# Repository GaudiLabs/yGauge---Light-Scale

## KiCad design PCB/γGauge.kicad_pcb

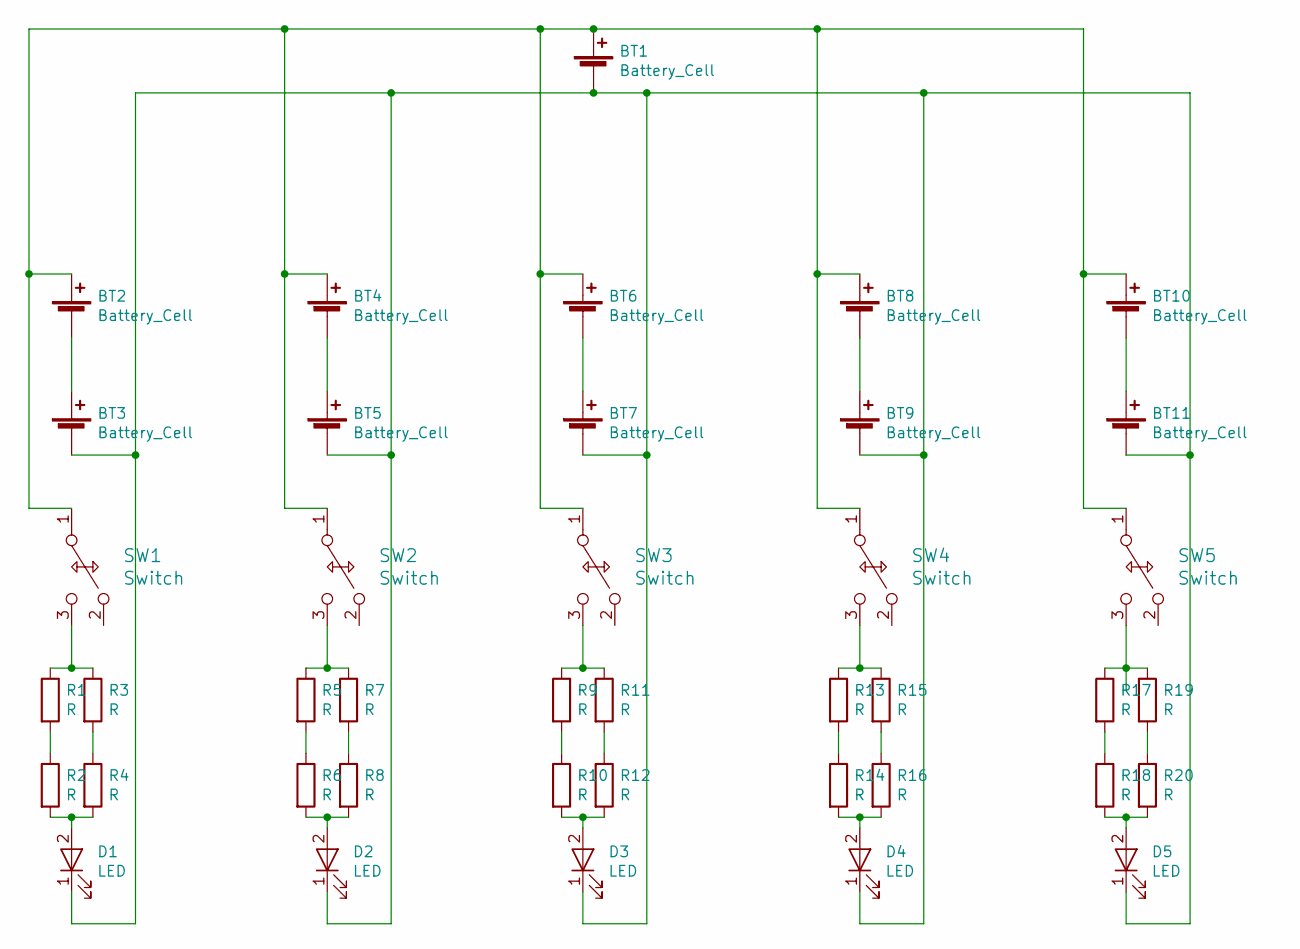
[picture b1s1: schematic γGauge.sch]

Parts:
BT1: Battery_Cell; CR2032_Holder
BT2, BT3, BT4, BT5, BT6, BT7, BT8, BT9, BT10, BT11: Battery_Cell; CELL_HOLDER_6_8
D1, D2, D3, D4, D5: LED; LP_T67K
R1, R2, R3, R4, R5, R6, R7, R8, R9, R10, R11, R12, R13, R14, R15, R16, R17, R18, R19, R20: R; SMD_LowZ
SW1, SW2, SW3, SW4, SW5: Switch; MSS22d18

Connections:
unnamed: BT1.1 (+), BT2.1 (+), BT4.1 (+), BT6.1 (+), BT8.1 (+), BT10.1 (+), SW1.1, SW2.1, SW3.1, SW4.1, SW5.1
unnamed: BT1.2 (-), BT3.2 (-), BT5.2 (-), BT7.2 (-), BT9.2 (-), BT11.2 (-), D1.1 (K), D2.1 (K), D3.1 (K), D4.1 (K), D5.1 (K)
unnamed: BT2.2 (-), BT3.1 (+)
unnamed: BT4.2 (-), BT5.1 (+)
unnamed: BT6.2 (-), BT7.1 (+)
unnamed: BT8.2 (-), BT9.1 (+)
unnamed: BT10.2 (-), BT11.1 (+)
unnamed: D1.2 (A), R2.2, R4.2
unnamed: D2.2 (A), R6.2, R8.2
unnamed: D3.2 (A), R10.2, R12.2
unnamed: D4.2 (A), R14.2, R16.2
unnamed: D5.2 (A), R18.2, R20.2
unnamed: R1.1, R3.1, SW1.3
unnamed: R1.2, R2.1
unnamed: R3.2, R4.1
unnamed: R5.1, R7.1, SW2.3
unnamed: R5.2, R6.1
unnamed: R7.2, R8.1
unnamed: R9.2, R10.1
unnamed: R9.1, R11.1, SW3.3
unnamed: R11.2, R12.1
unnamed: R13.1, R15.1, SW4.3
unnamed: R13.2, R14.1
unnamed: R15.2, R16.1
unnamed: R17.1, R19.1, SW5.3
unnamed: R17.2, R18.1
unnamed: R19.2, R20.1

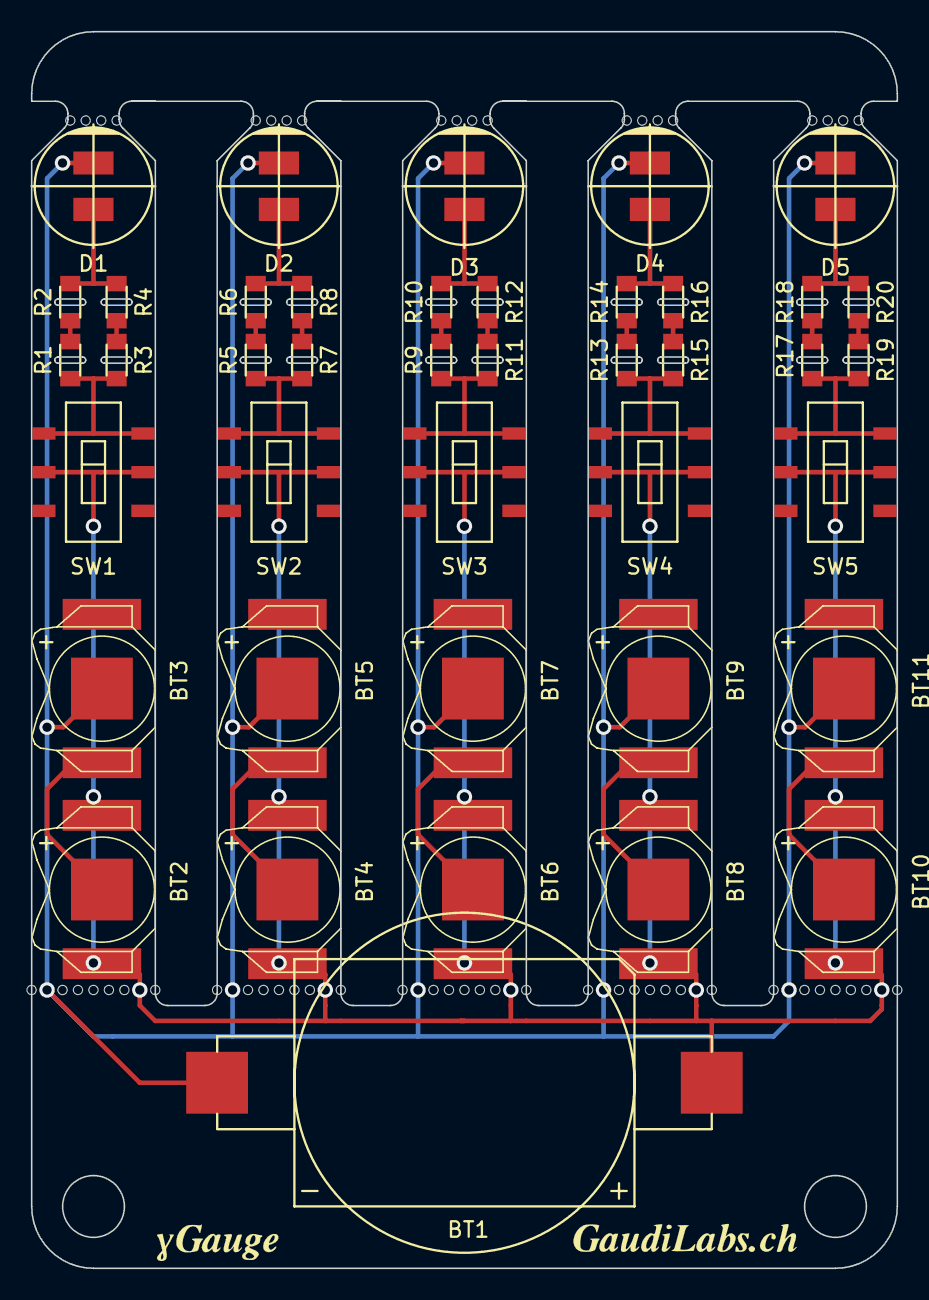
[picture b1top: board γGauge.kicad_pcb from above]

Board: 2 copper layers, 56.0 x 80.0 mm, 41 parts (0 on the bottom side), 27 nets.

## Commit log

2020-09-21 first upload of PCB yGauge
